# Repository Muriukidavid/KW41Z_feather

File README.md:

# KW41Z_feather 
 
A feather form factor for BLE, ZigBee or Thread node based on the NXP MKW41Z wireless microcontroller. This is work in progress and a completely untested design as at this point. 

## Preview

## Features 

* Feather header pins (custom mapping due to limited MCU pins)
* NXP MKW41Z Wireless MCU With a PCB antennae
* SWD Debug (using some of the feather header pins)
* USB to UART (CP2104) connected to the MCU UART terminal
* LiPo battery charger (SL4054ST25P) with a standard battery connector
* On board 5V to 3.3V regulator
* RTC oscillator
* Reset and user buttons
* Indicator LEDs (One user LED, two BLE activity LEDs) 

## Planned 

* Add U.FL connector for external antennae with a series selection resistor
* Add on-board SD card connector (back side)

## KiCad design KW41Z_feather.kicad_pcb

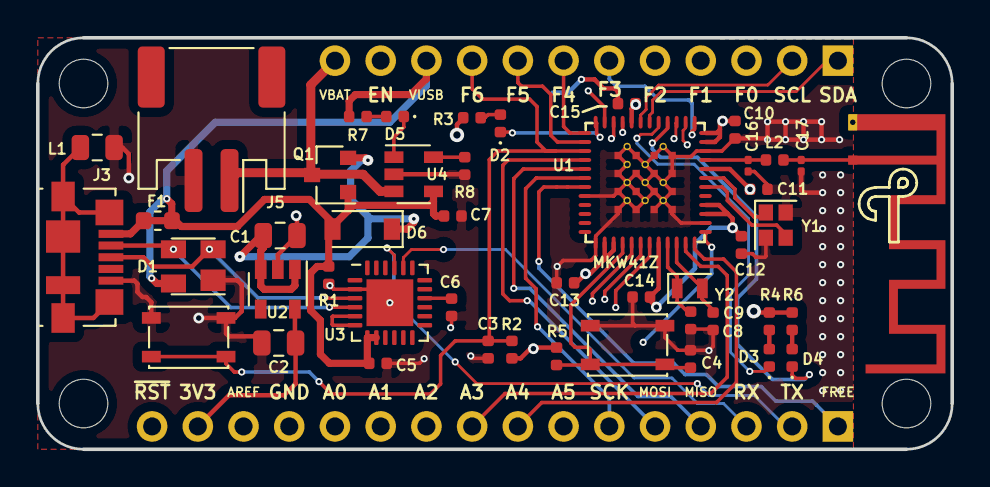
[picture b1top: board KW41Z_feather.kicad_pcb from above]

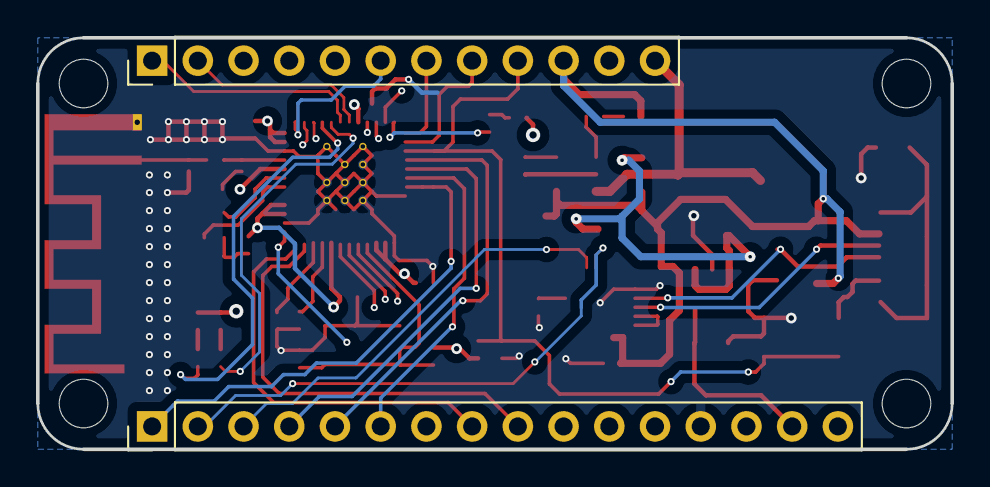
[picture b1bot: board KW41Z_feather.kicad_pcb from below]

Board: 4 copper layers, 50.8 x 22.9 mm, 48 parts (2 on the bottom side), 47 nets.

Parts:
ANT1: MEANDER_ANT_HORZ; Texas_SWRA117D_2.4GHz_Right
C1, C2: 10uF ±10% 25V X5R; C_0805_2012Metric
C3, C4, C5: 100nF; C_0402_1005Metric
C6: 4.7uF; C_0402_1005Metric
C7: 2.2uF; C_0402_1005Metric
C8, C9: DNP; C_0402_1005Metric
C10, C11, C12, C13, C14, C15: 100nF 25V ±10% X7R 0402; C_0402_1005Metric
C16, C17: CER 0.7pF 50V ±0.1pF C0G 0201; C_0201_0603Metric
D1: SP0503BAHT; SOT-143
D2, D5: LED Red 620nm@25mA; LED_0402_1005Metric
D3: LED Blue 470nm 20mA; LED_0402_1005Metric
D4: RED Green 520nm@5mA; LED_0402_1005Metric
D6: MBR0520-TP; D_SOD-123
F1: Fuse_Small; Fuse_0603_1608Metric
J1: feather long; PinHeader_1x16_P2.54mm_Vertical
J2: feather short; PinHeader_1x12_P2.54mm_Vertical
J3: USB_B_Micro; USB_Micro-B_Molex_47346-0001
J5: LiPo; JST_PH_S2B-PH-SM4-TB_1x02-1MP_P2.00mm_Horizontal
L1: bead; L_0805_2012Metric
L2: 5.6nH@500MHz 140mA ±1.78% 0402; L_0402_1005Metric
Q1: FDN340P; SOT-23
R1: 1K ±5% 1/4W 0402; R_0402_1005Metric
R2, R5: 10K ±5% 1/4W 0402; R_0402_1005Metric
R3, R4, R6, R7: 330Ω ±5% 1/16W; R_0402_1005Metric
R8: 2KΩ ±5% 1/16W; R_0402_1005Metric
SW1, SW2: PTS810; SW_SPST_PTS810
U1: MKW41Z512VHT4; MKW41Z512VHT4_A
U2: XC6220B331MR; SOT-23-5
U3: CP2104; QFN-24-1EP_4x4mm_P0.5mm_EP2.6x2.6mm
U4: SL4054ST25P; SOT-23-5
Y1: 32Mhz ±10ppm 12pF; Crystal_SMD_2016-4Pin_2.0x1.6mm
Y2: 32.768KHz ±20ppm 7pF; Crystal_SMD_2012-2Pin_2.0x1.2mm

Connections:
+3V3: C2.1, C10.1, C11.1, C12.1, C13.1, C14.1, C15.1, J1.15, R2.1, R3.1, R4.1, R5.1, R6.1, U1.14, U1.15, U1.20, U1.27, U1.28, U1.32, U1.35, U1.36, U1.44, U2.5
/A0: J1.12, U1.17
/A1: J1.11, U1.18
/A2: J1.10, U1.19
/A3: J1.9, U1.23
/A4: J1.8, U1.24
/A5: J1.7, U1.25
/CS: J1.1, U1.7
/F0: J2.3, U1.45
/F1: J2.4, U1.46
/F2: J2.5, U1.47
/F3: J2.6, U1.37
/MISO: J1.4, U1.5
/MOSI: J1.5, U1.4
/SCK: J1.6, U1.6
/SCL: J2.1, U1.42
/SDA: J2.2, U1.43
/debug_power_and_usb/VIN: C1.1, D6.1, Q1.2, U2.1, U2.3
ANT: C16.1, L2.1, U1.33
BAT: J2.12, J5.1, Q1.3, U4.3
BTN: C4.1, R5.2, SW2.2, U1.16
EXTAL0: U1.30, Y1.3
EXTAL_32: C8.2, U1.21, Y2.1
GND: ANT1.2, C1.2, C2.2, C3.2, C4.2, C5.1, C6.1, C7.2, C8.1, C9.1, C10.2, C11.2, C12.2, C13.2, C14.2, C15.2, C16.2, C17.2, D1.1, J1.13, J3.5, J5.2, L1.2, R1.2, R8.2, SW1.1, SW2.1, U1.8, U1.13, U1.26, U1.34, U1.49, U1.50, U1.51, U1.52, U1.53, U1.54, U1.55, U1.56, U1.57, U1.58, U1.59, U1.60, U1.61, U1.62, U1.63, U1.64, U2.2, U3.2, U3.25, U4.2, Y1.2, Y1.4
LED1: D2.1, U1.48
LED2: D3.1, U1.41
LED3: D4.1, U1.40
unnamed: ANT1.1, C17.1, L2.2
unnamed: C6.2, U3.16
unnamed: D2.2, R3.2
unnamed: D3.2, R4.2
unnamed: D4.2, R6.2
unnamed: D5.1, U4.1
unnamed: D5.2, R7.2
unnamed: J3.6, L1.1
unnamed: R8.1, U4.5
unnamed: U3.5, U3.6
RESET: C3.1, J2.9, R2.2, SW1.2, U1.3
RX: J1.3, U1.38, U3.20
SWD_CLK: J2.8, U1.2
SWD_IO: J2.7, U1.1
TX: J1.2, U1.39, U3.21
USB+: D1.2, J3.3, U3.3
USB-: D1.3, J3.2, U3.4
VUSB: C5.2, C7.1, D1.4, D6.2, F1.1, F1.2, J2.10, J3.1, Q1.1, R1.1, R7.1, U3.7, U3.8, U4.4
XTAL0: U1.31, Y1.1
XTAL_32: C9.2, U1.22, Y2.2

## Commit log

2020-09-26 Add initial design files
    Capture Schematic
    Add PCB layout design
    Add some missing 3D models
    Add a bit of information in README
    Add a few datasheets
